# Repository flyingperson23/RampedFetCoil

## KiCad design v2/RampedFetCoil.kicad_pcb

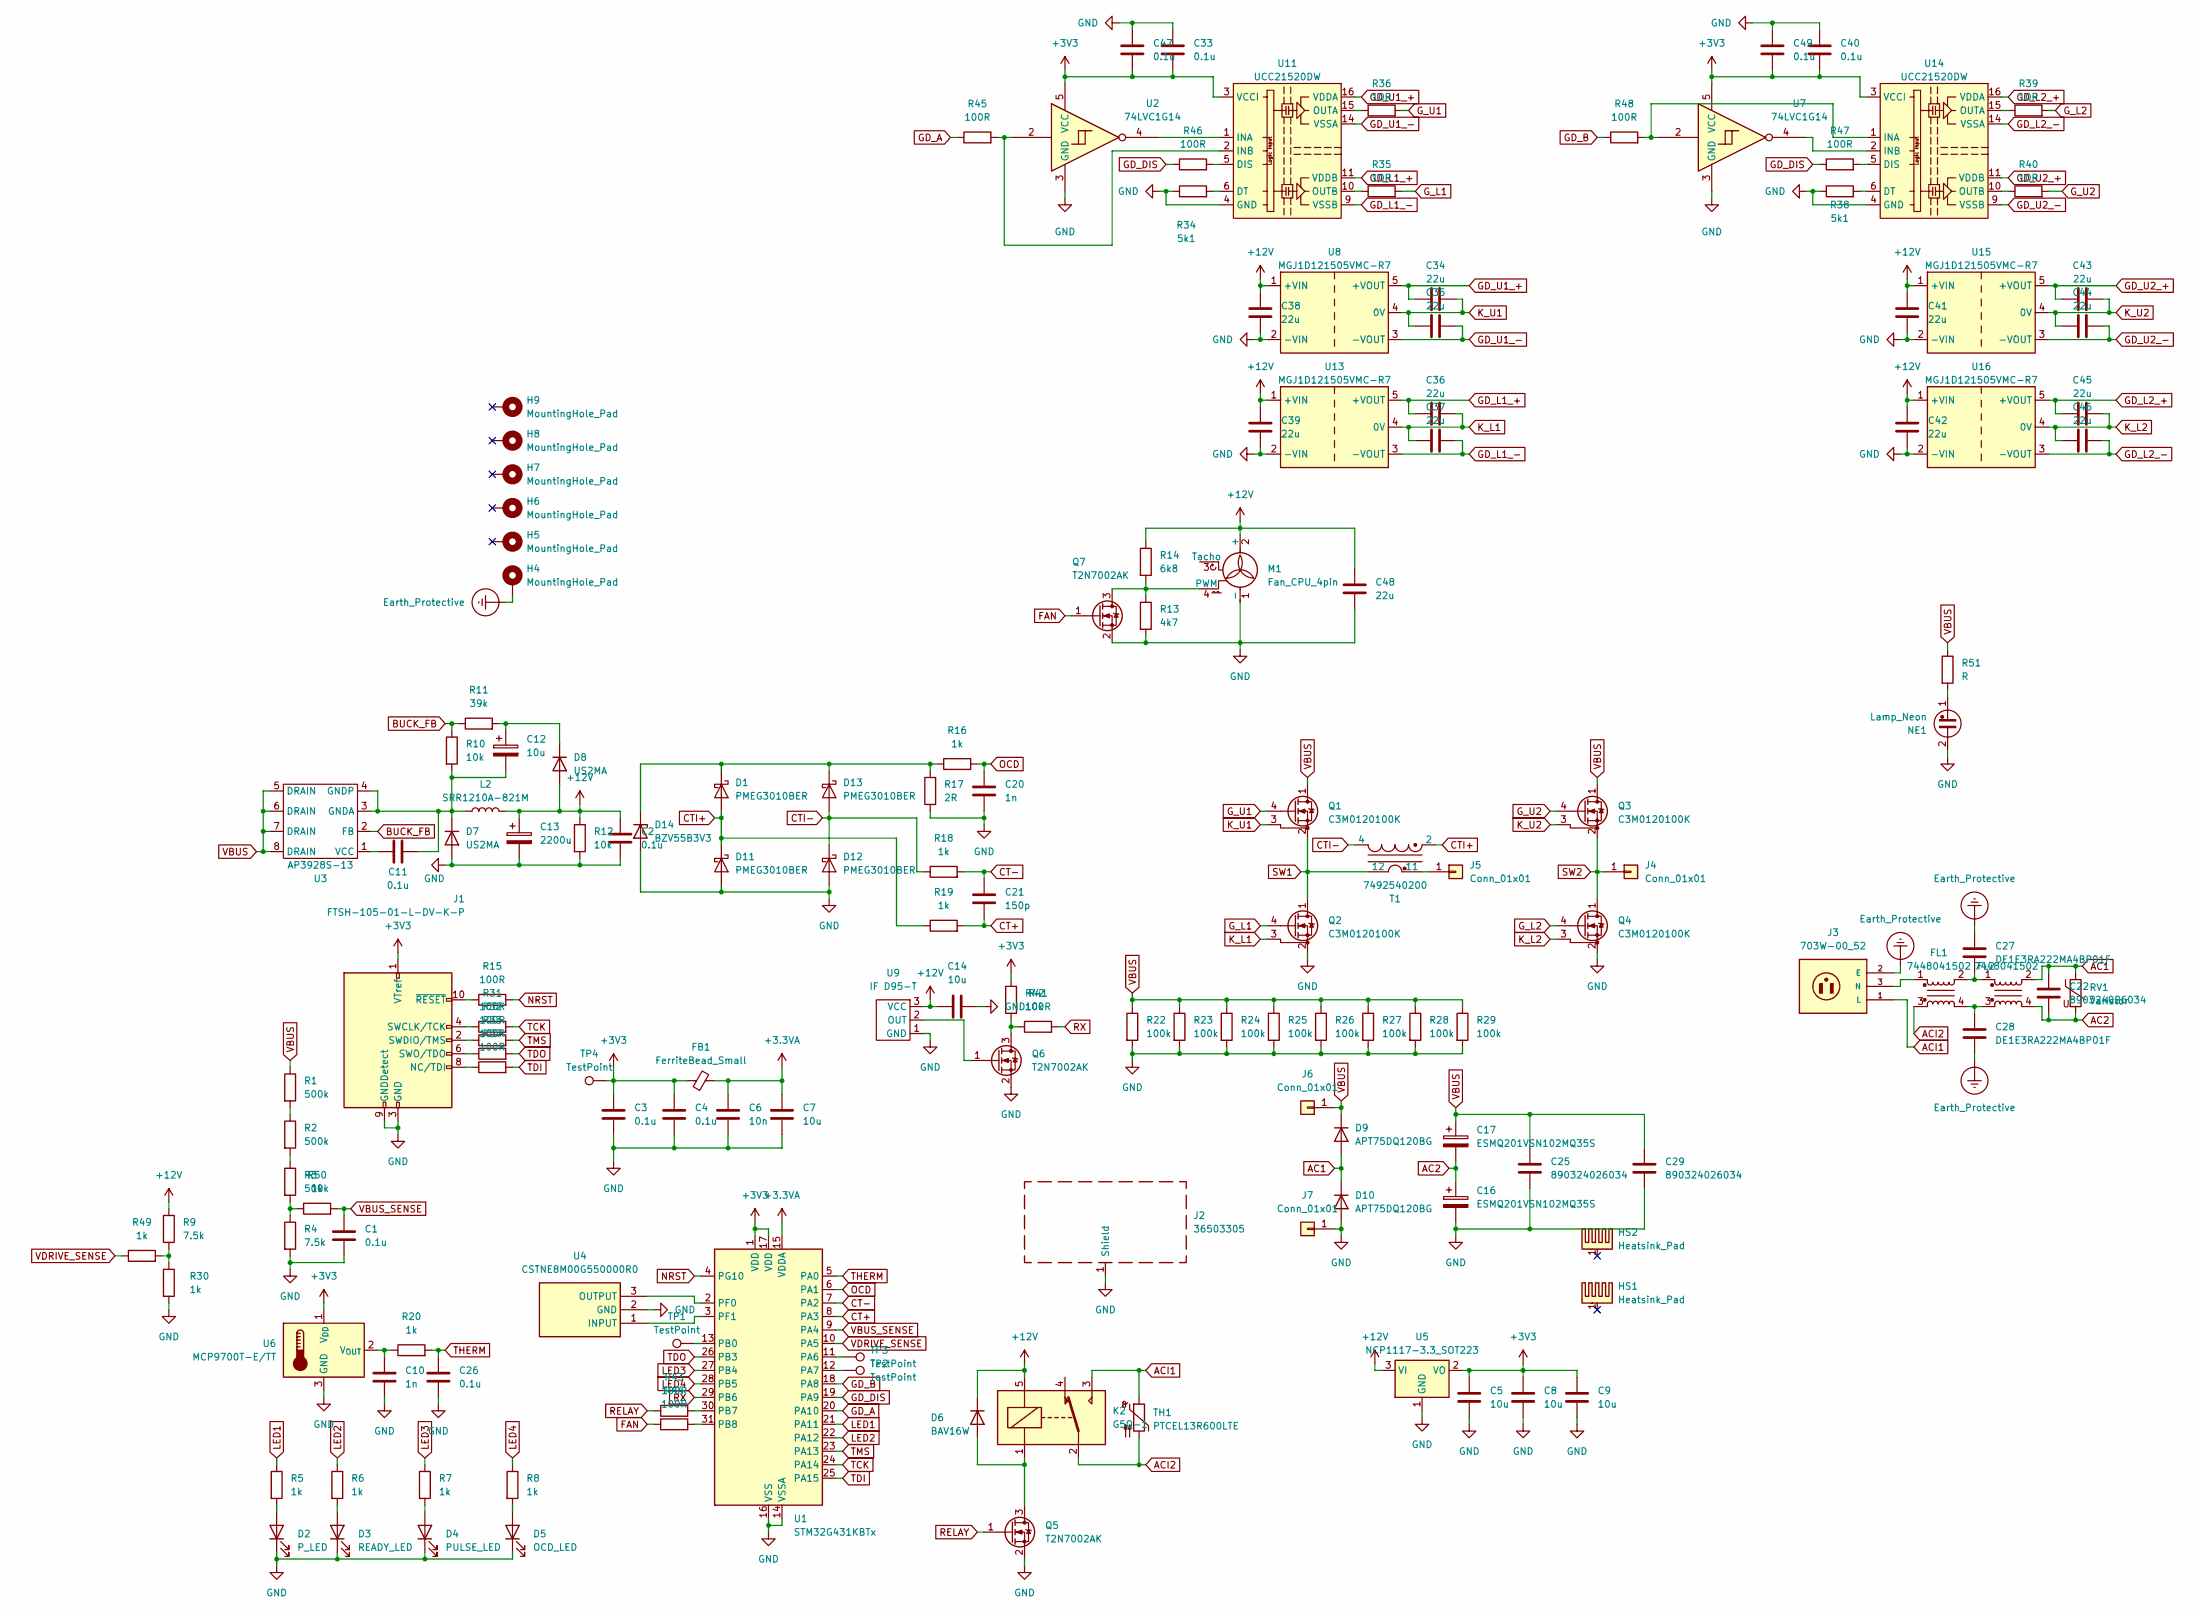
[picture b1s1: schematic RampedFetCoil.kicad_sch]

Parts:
C1, C2, C3, C4, C11, C26, C33, C40, C47, C49: 0.1u; C_0805_2012Metric
C5, C7, C8, C9, C14: 10u; C_0805_2012Metric
C6: 10n; C_0805_2012Metric
C10, C20: 1n; C_0805_2012Metric
C12: 10u; 860010572002; MPN 860010572002
C13: 2200u; 2m2 25V 860010478021; MPN 860020575013
C16, C17: ESMQ201VSN102MQ35S
C21: 150p; C_0805_2012Metric
C22, C25, C29: 890324026034
C27, C28: DE1E3RA222MA4BP01F
C34, C35, C36, C37, C38, C39, C41, C42, C43, C44, C45, C46, C48: 22u; C_1210_3225Metric
D1, D11, D12, D13: PMEG3010BER; Nexperia_CFP3_SOD-123W
D2: P_LED; LED_0805_2012Metric
D3: READY_LED; LED_0805_2012Metric
D4: PULSE_LED; LED_0805_2012Metric
D5: OCD_LED; LED_0805_2012Metric
D6: BAV16W; D_SOD-123
D7, D8: US2MA; D_SMA
D9, D10: APT75DQ120BG; TO-247-2_Vertical
D14: BZV55B3V3; D_MiniMELF
FB1: FerriteBead_Small; L_0805_2012Metric
FL1, FL2: 7448041502
H4, H5, H6, H7, H8, H9: MountingHole_Pad; MountingHole_4.3mm_M4_Pad_Via
HS1: Heatsink_Pad; C40
HS2: Heatsink_Pad; C40_Half
J1: FTSH-105-01-L-DV-K-P; PinHeader_2x05_P1.27mm_Vertical_SMD
J2: 36503305; Wuerth_36503305_30x30mm
J3: 703W-00_52; QUALTEK_703W-00_52; PARTREV B
J4, J5, J6, J7: Conn_01x01; SPADE_726386-2
K2: G5Q-1; Relay_SPDT_Omron-G5Q-1
L2: SRR1210A-821M; L_Bourns_SRR1210A
M1: Fan_CPU_4pin; FanPinHeader_1x04_P2.54mm_Vertical
NE1: Lamp_Neon; NEON-A1A
Q1, Q2, Q3, Q4: C3M0120100K; TO-247-4_Vertical
Q5, Q6, Q7: T2N7002AK; SOT-23
R1, R2, R3: 500k; R_0805_2012Metric
R4, R9: 7.5k; R_0805_2012Metric
R5, R6, R7, R8, R16, R18, R19, R20, R30, R49, R50: 1k; R_0805_2012Metric
R10, R12, R42: 10k; R_0805_2012Metric
R11: 39k; R_0805_2012Metric
R13: 4k7; R_0805_2012Metric
R14: 6k8; R_0805_2012Metric
R15, R31, R32, R33, R37, R41, R43, R44, R45, R46, R47, R48: 100R; R_0805_2012Metric
R17: 2R; R_2512_6332Metric
R22, R23, R24, R25, R26, R27, R28, R29: 100k; R_2512_6332Metric
R34, R38: 5k1; R_0805_2012Metric
R35, R36, R39, R40: 10R; R_0805_2012Metric
R51: R; R_Axial_DIN0207_L6.3mm_D2.5mm_P2.54mm_Vertical
RV1: Varistor; RV_Disc_D15.5mm_W3.9mm_P7.5mm
T1: 7492540200
TH1: PTCEL13R600LTE; THERMISTOR_PTCEL13_5MM_VIS
TP1, TP2, TP3, TP4: TestPoint; TestPoint_Pad_1.5x1.5mm
U1: STM32G431KBTx; LQFP-32_7x7mm_P0.8mm
U2, U7: 74LVC1G14; SOT-23-5
U3: AP3928S-13; SO-8_3.9x4.9mm_P1.27mm
U4: CSTNE8M00G550000R0; Resonator_SMD_Murata_CSTxExxV-3Pin_3.0x1.1mm; Mouser Part Number 81-CSTNE8M00G550000R
U5: NCP1117-3.3_SOT223; SOT-223-3_TabPin2
U6: MCP9700T-E/TT; SOT-23
U8, U13, U15, U16: MGJ1D121505VMC-R7; MGJ1V
U9: IF D95-T; IF-D95
U11, U14: UCC21520DW; SOIC-16W_7.5x10.3mm_P1.27mm

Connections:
+3.3VA: C6.1, C7.1, FB1.2, U1.15 (VDDA)
+3V3: C3.1, C4.1, C5.1, C8.1, C9.1, C33.2, C40.2, C47.2, C49.2, FB1.1, J1.1 (VTref), R42.2, TP4.1, U1.1 (VDD), U1.17 (VDD), U2.5 (VCC), U5.2 (VO), U6.1 (V_{DD}), U7.5 (VCC), U11.3 (VCCI), U11.8 (VCCI), U14.3 (VCCI), U14.8 (VCCI)
+12V: C2.1, C13.1, C14.1, C38.2, C39.2, C41.2, C42.2, C48.2, D6.1 (K), D8.2 (A), K2.5, L2.2, M1.2 (+), R9.1, R12.1, R14.1, U5.3 (VI), U8.1 (+VIN), U9.3 (VCC), U13.1 (+VIN), U15.1 (+VIN), U16.1 (+VIN)
AC1: C22.1, D9.2 (A), D10.1 (K), FL2.2, RV1.1
AC2: C16.1, C17.2, C22.2, FL2.4, RV1.2
ACI1: J3.1 (L), K2.3, TH1.1
ACI2: FL1.3, K2.2, TH1.2
BUCK_FB: R10.1, R11.1, U3.2 (FB)
CT+: C21.2, R19.2, U1.8 (PA3)
CT-: C21.1, R18.2, U1.7 (PA2)
CTI+: D1.2 (A), D11.1 (K), R19.1, T1.2
CTI-: D12.1 (K), D13.2 (A), R18.1, T1.4
Earth_Protective: C27.1, C28.2, H4.1, J3.2 (E)
FAN: Q7.1 (G), R44.1
GD_A: R45.1, U1.20 (PA10)
GD_B: R48.1, U1.18 (PA8)
GD_DIS: R46.1, R47.1, U1.19 (PA9)
GD_L1_+: C36.1, U11.11 (VDDB), U13.5 (+VOUT)
GD_L1_-: C37.2, U11.9 (VSSB), U13.3 (-VOUT)
GD_L2_+: C45.1, U14.16 (VDDA), U16.5 (+VOUT)
GD_L2_-: C46.2, U14.14 (VSSA), U16.3 (-VOUT)
GD_U1_+: C34.1, U8.5 (+VOUT), U11.16 (VDDA)
GD_U1_-: C35.2, U8.3 (-VOUT), U11.14 (VSSA)
GD_U2_+: C43.1, U14.11 (VDDB), U15.5 (+VOUT)
GD_U2_-: C44.2, U14.9 (VSSB), U15.3 (-VOUT)
GND: C1.2, C2.2, C3.2, C4.2, C5.2, C6.2, C7.2, C8.2, C9.2, C10.2, C13.2, C14.2, C16.2, C20.2, C25.2, C26.2, C29.2, C33.1, C38.1, C39.1, C40.1, C41.1, C42.1, C47.1, C48.1, C49.1, D2.1 (K), D3.1 (K), D4.1 (K), D5.1 (K), D7.2 (A), D10.2 (A), D11.2 (A), D12.2 (A), D14.2 (A), J1.3 (GND), J1.5 (GND), J1.9 (GNDDetect), J2.1 (Shield), J7.1, M1.1 (-), NE1.2, Q2.2 (S), Q4.2 (S), Q5.2 (S), Q6.2 (S), Q7.2 (S), R4.2, R12.2, R13.2, R17.1, R22.2, R23.2, R24.2, R25.2, R26.2, R27.2, R28.2, R29.2, R30.2, R34.1, R38.1, U1.14 (VSSA), U1.16 (VSS), U1.32 (VSS), U2.3 (GND), U4.2 (GND), U5.1 (GND), U6.3 (GND), U7.3 (GND), U8.2 (-VIN), U9.1 (GND), U11.4 (GND), U13.2 (-VIN), U14.4 (GND), U15.2 (-VIN), U16.2 (-VIN)
G_L1: Q2.4 (G), R35.2
G_L2: Q4.4 (G), R39.2
G_U1: Q1.4 (G), R36.2
G_U2: Q3.4 (G), R40.2
K_L1: C36.2, C37.1, Q2.3 (DS), U13.4 (0V)
K_L2: C45.2, C46.1, Q4.3 (DS), U16.4 (0V)
K_U1: C34.2, C35.1, Q1.3 (DS), U8.4 (0V)
K_U2: C43.2, C44.1, Q3.3 (DS), U15.4 (0V)
LED1: R5.1, U1.21 (PA11)
LED2: R6.1, U1.22 (PA12)
LED3: R7.1, U1.27 (PB4)
LED4: R8.1, U1.28 (PB5)
NRST: R15.2, U1.4 (PG10)
unnamed: C27.2, FL1.2, FL2.1
unnamed: C28.1, FL1.4, FL2.3
unnamed: D1.1 (K), D13.1 (K), D14.1 (K), R16.1, R17.2
unnamed: D2.2 (A), R5.2
unnamed: D3.2 (A), R6.2
unnamed: D4.2 (A), R7.2
unnamed: D5.2 (A), R8.2
unnamed: D6.2 (A), K2.1, Q5.3 (D)
unnamed: C11.1, C12.2, D7.1 (K), L2.1, R10.2, U3.3 (GNDA), U3.4 (GNDP)
unnamed: C12.1, D8.1 (K), R11.2
unnamed: J1.8 (NC/TDI), R37.1
unnamed: J1.4 (SWCLK/TCK), R31.1
unnamed: J1.2 (SWDIO/TMS), R32.1
unnamed: J1.6 (SWO/TDO), R33.1
unnamed: J1.10 (~RESET), R15.1
unnamed: FL1.1, J3.3 (N)
unnamed: J5.1, T1.11
unnamed: M1.4 (PWM), Q7.3 (D), R13.1, R14.2
unnamed: NE1.1, R51.2
unnamed: Q6.3 (D), R41.1, R42.1
unnamed: Q6.1 (G), U9.2 (OUT)
unnamed: R1.2, R2.1
unnamed: R2.2, R3.1
unnamed: R3.2, R4.1, R50.1
unnamed: R9.2, R30.1, R49.2
unnamed: TP3.1, U1.11 (PA6)
unnamed: TP2.1, U1.12 (PA7)
unnamed: TP1.1, U1.13 (PB0)
unnamed: R43.2, U1.30 (PB7)
unnamed: R44.2, U1.31 (PB8)
unnamed: U1.2 (PF0), U4.3 (OUTPUT)
unnamed: U1.3 (PF1), U4.1 (INPUT)
unnamed: C11.2, U3.1 (VCC)
unnamed: C10.1, R20.1, U6.2 (V_{OUT})
unnamed: R46.2, U11.5 (DIS)
unnamed: R34.2, U11.6 (DT)
unnamed: U2.4, U11.1 (INA)
unnamed: R45.2, U2.2, U11.2 (INB)
unnamed: R36.1, U11.15 (OUTA)
unnamed: R35.1, U11.10 (OUTB)
unnamed: R47.2, U14.5 (DIS)
unnamed: R38.2, U14.6 (DT)
unnamed: R48.2, U7.2, U14.1 (INA)
unnamed: U7.4, U14.2 (INB)
unnamed: R39.1, U14.15 (OUTA)
unnamed: R40.1, U14.10 (OUTB)
OCD: C20.1, R16.2, U1.6 (PA1)
RELAY: Q5.1 (G), R43.1
RX: R41.2, U1.29 (PB6)
SW1: Q1.2 (S), Q2.1 (D), T1.12
SW2: J4.1, Q3.2 (S), Q4.1 (D)
TCK: R31.2, U1.24 (PA14)
TDI: R37.2, U1.25 (PA15)
TDO: R33.2, U1.26 (PB3)
THERM: C26.1, R20.2, U1.5 (PA0)
TMS: R32.2, U1.23 (PA13)
VBUS: C17.1, C25.1, C29.1, D9.1 (K), J6.1, Q1.1 (D), Q3.1 (D), R1.1, R22.1, R23.1, R24.1, R25.1, R26.1, R27.1, R28.1, R29.1, R51.1, U3.5 (DRAIN), U3.6 (DRAIN), U3.7 (DRAIN), U3.8 (DRAIN)
VBUS_SENSE: C1.1, R50.2, U1.9 (PA4)
VDRIVE_SENSE: R49.1, U1.10 (PA5)

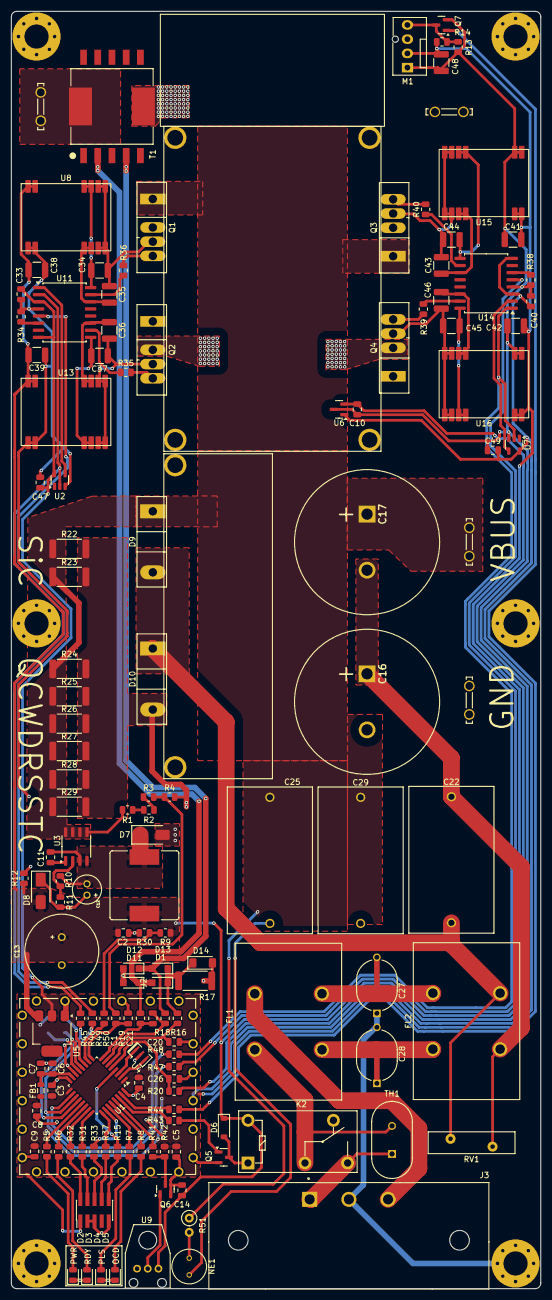
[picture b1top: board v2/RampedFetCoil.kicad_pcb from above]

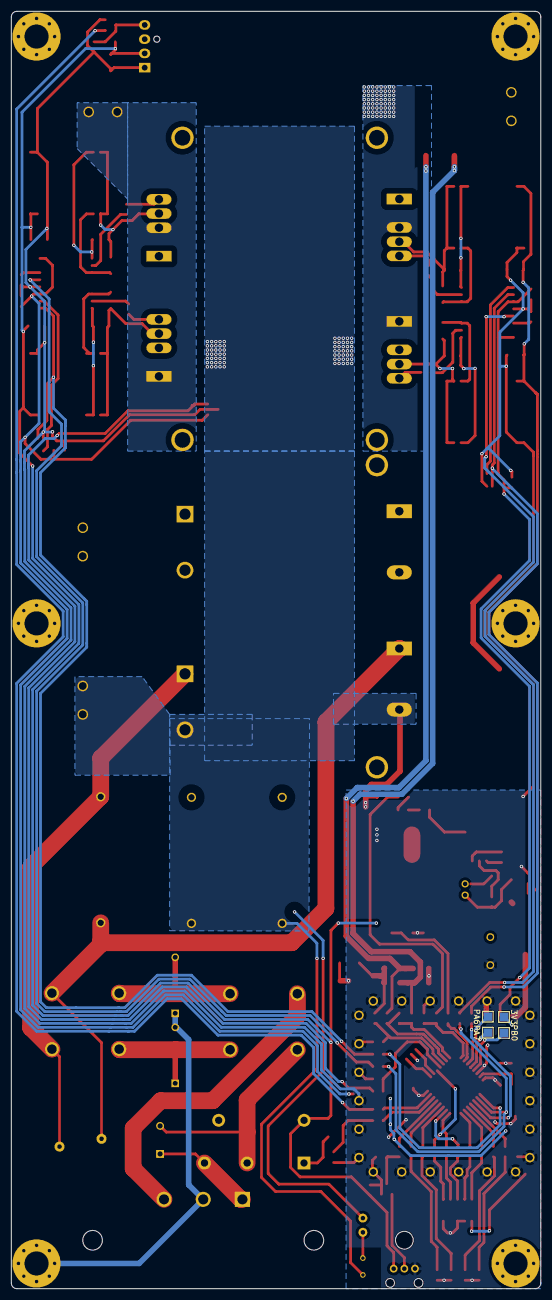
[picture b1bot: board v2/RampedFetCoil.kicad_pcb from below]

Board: 2 copper layers, 94.5 x 228.0 mm, 155 parts (4 on the bottom side), 98 nets.

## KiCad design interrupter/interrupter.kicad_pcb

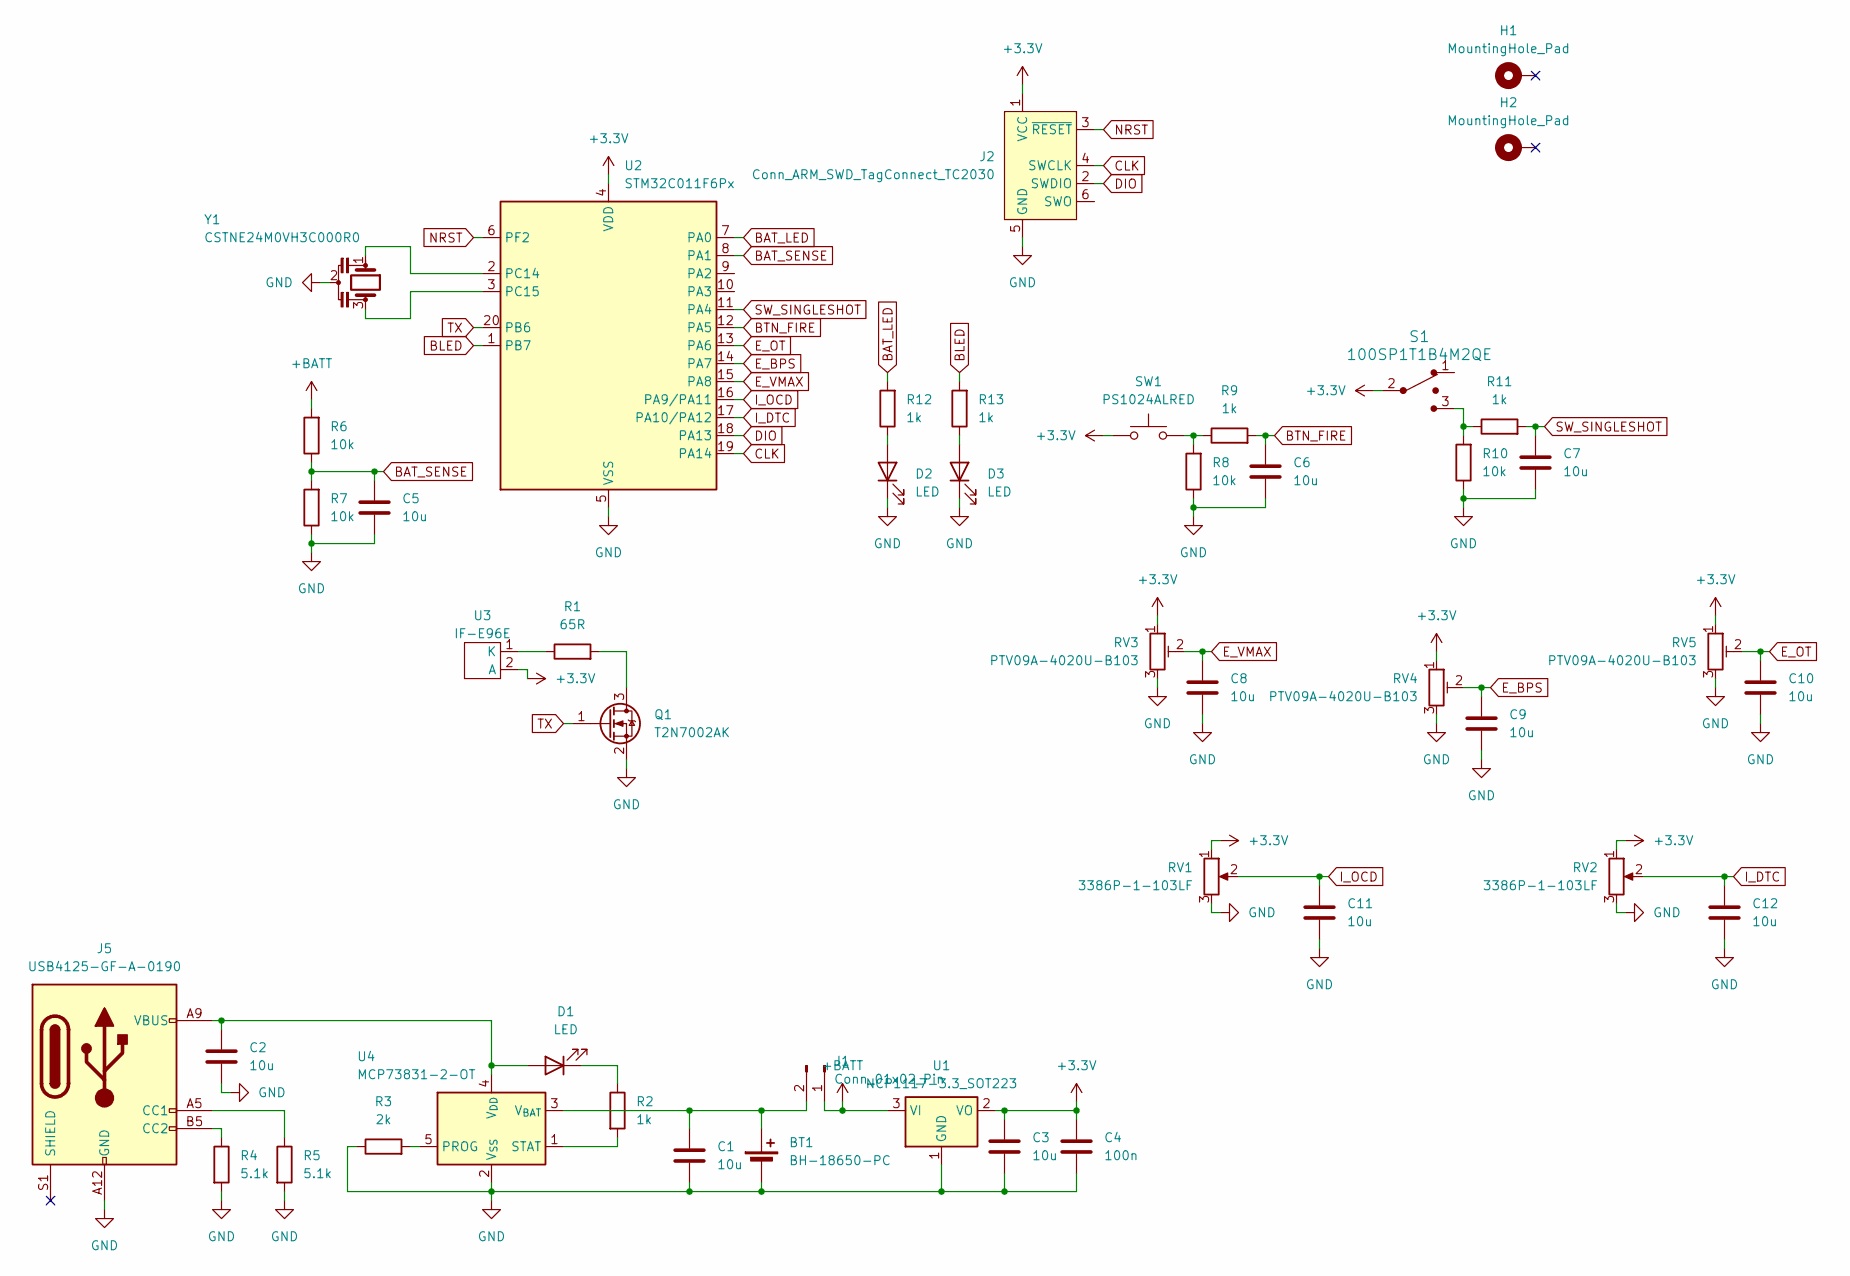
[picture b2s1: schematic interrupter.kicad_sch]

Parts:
BT1: BH-18650-PC; BatteryHolder_MPD_BH-18650-PC2
C1, C2, C3, C5, C6, C7, C8, C9, C10, C11, C12: 10u; C_0805_2012Metric
C4: 100n; C_0805_2012Metric
D1, D2, D3: LED; LED_0805_2012Metric
H1, H2: MountingHole_Pad; MountingHole_2.7mm_M2.5_Pad_Via
J1: Conn_01x02_Pin; Molex_KK-254_AE-6410-02A_1x02_P2.54mm_Vertical
J2: Conn_ARM_SWD_TagConnect_TC2030; Tag-Connect_TC2030-IDC-FP_2x03_P1.27mm_Vertical
J5: USB4125-GF-A-0190; USB_C_Receptacle_GCT_USB4125-xx-x-0190_6P_TopMnt_Horizontal
Q1: T2N7002AK; SOT-23
R1: 65R; R_0805_2012Metric
R2, R9, R11, R12, R13: 1k; R_0805_2012Metric
R3: 2k; R_0805_2012Metric
R4, R5: 5.1k; R_0805_2012Metric
R6, R7, R8, R10: 10k; R_0805_2012Metric
RV1, RV2: 3386P-1-103LF; Potentiometer_Bourns_3386P_Vertical
RV3, RV4, RV5: PTV09A-4020U-B103; Potentiometer_Bourns_PTV09A-1_Single_Vertical
S1: 100SP1T1B4M2QE; Toggle_Switch_100SP1T1B4M2QE; MPN 100SP1T1B4M2QE; Digi-Key_PN EG2355-ND
SW1: PS1024ALRED; SW_PS1024ALRED
U1: NCP1117-3.3_SOT223; SOT-223-3_TabPin2
U2: STM32C011F6Px; TSSOP-20_4.4x6.5mm_P0.65mm
U3: IF-E96E
U4: MCP73831-2-OT; SOT-23-5
Y1: CSTNE24M0VH3C000R0; Resonator_SMD_Murata_CSTxExxV-3Pin_3.0x1.1mm

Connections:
+3.3V: C3.1, C4.1, J2.1 (VCC), RV1.1, RV2.1, RV3.1, RV4.1, RV5.1, S1.2 (Com), SW1.1, U1.2 (VO), U2.4 (VDD), U3.2 (A)
+BATT: J1.1, R6.2, U1.3 (VI)
BAT_LED: R12.2, U2.7 (PA0)
BAT_SENSE: C5.1, R6.1, R7.2, U2.8 (PA1)
BLED: R13.2, U2.1 (PB7)
BTN_FIRE: C6.1, R9.2, U2.12 (PA5)
CLK: J2.4 (SWCLK), U2.19 (PA14)
DIO: J2.2 (SWDIO), U2.18 (PA13)
E_BPS: C9.1, RV4.2, U2.14 (PA7)
E_OT: C10.1, RV5.2, U2.13 (PA6)
E_VMAX: C8.1, RV3.2, U2.15 (PA8)
GND: BT1.2 (-), C1.2, C2.2, C3.2, C4.2, C5.2, C6.2, C7.2, C8.2, C9.2, C10.2, C11.2, C12.2, D2.1 (K), D3.1 (K), J2.5 (GND), J5.A12 (GND), J5.B12 (GND), Q1.2 (S), R3.1, R4.2, R5.2, R7.1, R8.1, R10.1, RV1.3, RV2.3, RV3.3, RV4.3, RV5.3, U1.1 (GND), U2.5 (VSS), U4.2 (V_{SS}), Y1.2
I_DTC: C12.1, RV2.2, U2.17 (PA10/PA12)
I_OCD: C11.1, RV1.2, U2.16 (PA9/PA11)
NRST: J2.3 (~RESET), U2.6 (PF2)
unnamed: BT1.1 (+), C1.1, J1.2, U4.3 (V_{BAT})
unnamed: C2.1, D1.2 (A), J5.A9 (VBUS), J5.B9 (VBUS), U4.4 (V_{DD})
unnamed: D1.1 (K), R2.1
unnamed: D2.2 (A), R12.1
unnamed: D3.2 (A), R13.1
unnamed: J5.A5 (CC1), R5.1
unnamed: J5.B5 (CC2), R4.1
unnamed: Q1.3 (D), R1.2
unnamed: R8.2, R9.1, SW1.2
unnamed: R10.2, R11.1, S1.3
unnamed: U2.2 (PC14), Y1.1
unnamed: U2.3 (PC15), Y1.3
unnamed: R1.1, U3.1 (K)
unnamed: R3.2, U4.5 (PROG)
unnamed: R2.2, U4.1 (STAT)
SW_SINGLESHOT: C7.1, R11.2, U2.11 (PA4)
TX: Q1.1 (G), U2.20 (PB6)

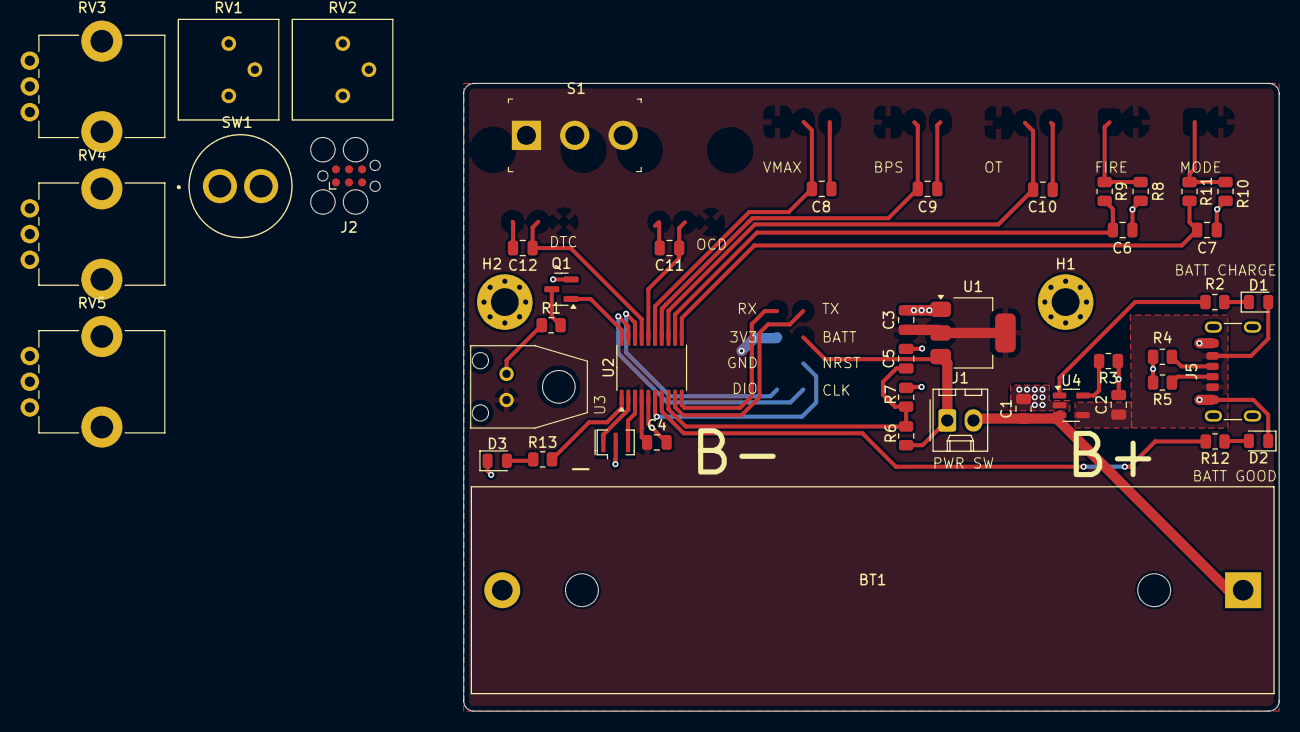
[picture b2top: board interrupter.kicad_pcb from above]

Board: 2 copper layers, 79.2 x 61.0 mm, 47 parts (0 on the bottom side), 32 nets.

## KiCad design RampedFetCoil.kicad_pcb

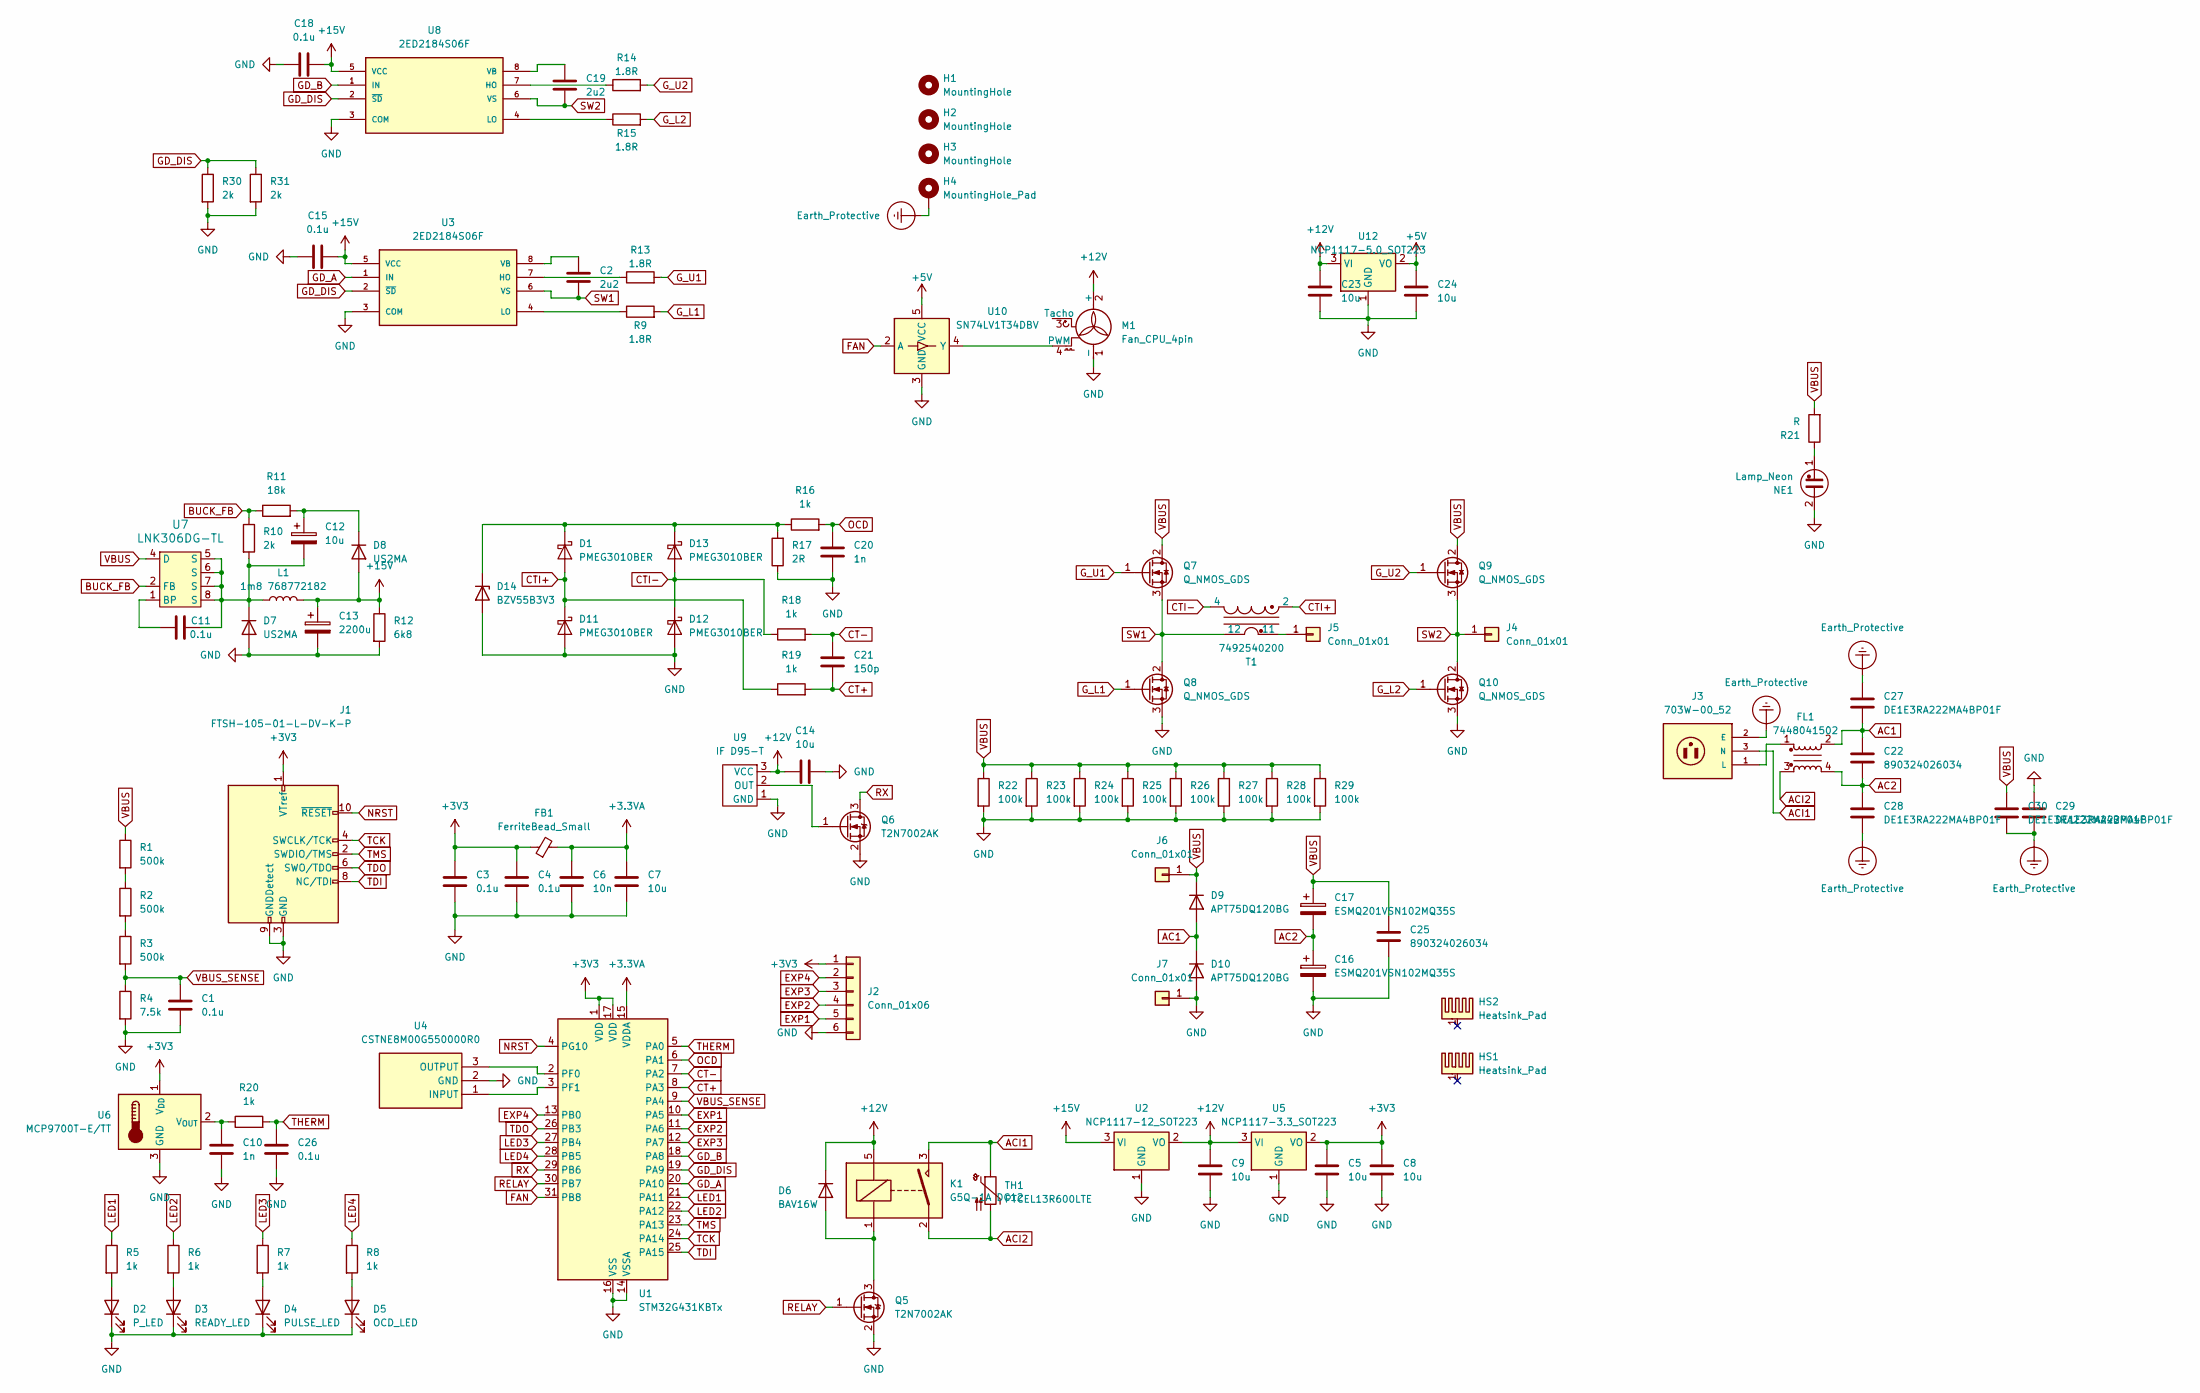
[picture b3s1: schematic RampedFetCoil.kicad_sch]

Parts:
C1, C3, C4, C11, C15, C18, C26: 0.1u; C_0805_2012Metric
C2, C19: 2u2; C_0805_2012Metric
C5, C7, C8, C9, C14, C23, C24: 10u; C_0805_2012Metric
C6: 10n; C_0805_2012Metric
C10, C20: 1n; C_0805_2012Metric
C12: 10u; 860010572002; MPN 860010572002
C13: 2200u; 2m2 25V 860010478021; MPN 860020575013
C16, C17: ESMQ201VSN102MQ35S
C21: 150p; C_0805_2012Metric
C22, C25: 890324026034
C27, C28, C29, C30: DE1E3RA222MA4BP01F
D1, D11, D12, D13: PMEG3010BER; Nexperia_CFP3_SOD-123W
D2: P_LED; LED_0805_2012Metric
D3: READY_LED; LED_0805_2012Metric
D4: PULSE_LED; LED_0805_2012Metric
D5: OCD_LED; LED_0805_2012Metric
D6: BAV16W; D_SOD-123
D7, D8: US2MA; D_SMA
D9, D10: APT75DQ120BG; TO-247-2_Vertical
D14: BZV55B3V3; D_MiniMELF
FB1: FerriteBead_Small; L_0805_2012Metric
FL1: 7448041502
H1, H2, H3: MountingHole; MountingHole_4.3mm_M4
H4: MountingHole_Pad; MountingHole_4.3mm_M4_Pad_Via
HS1: Heatsink_Pad; C40
HS2: Heatsink_Pad; C40_Half
J1: FTSH-105-01-L-DV-K-P; PinHeader_2x05_P1.27mm_Vertical_SMD
J2: Conn_01x06; PinHeader_1x06_P2.54mm_Vertical
J3: 703W-00_52; QUALTEK_703W-00_52; PARTREV B
J4, J5, J6, J7: Conn_01x01; SPADE_726386-2
K1: G5Q-1A DC12; Relay_SPST_Omron-G5Q-1A
L1: 1m8 768772182; WE-TI_809591; MPN 768772182
M1: Fan_CPU_4pin; FanPinHeader_1x04_P2.54mm_Vertical
NE1: Lamp_Neon; NEON-A1A
Q5, Q6: T2N7002AK; SOT-23
Q7, Q8, Q9, Q10: Q_NMOS_GDS; TO-247-3_Vertical
R1, R2, R3: 500k; R_0805_2012Metric
R4: 7.5k; R_0805_2012Metric
R5, R6, R7, R8, R16, R18, R19, R20: 1k; R_0805_2012Metric
R9, R13, R14, R15: 1.8R; R_0805_2012Metric
R10, R30, R31: 2k; R_0805_2012Metric
R11: 18k; R_0805_2012Metric
R12: 6k8; R_0805_2012Metric
R17: 2R; R_2512_6332Metric
R21: R; R_Axial_DIN0207_L6.3mm_D2.5mm_P10.16mm_Horizontal
R22, R23, R24, R25, R26, R27, R28, R29: 100k; R_2512_6332Metric
T1: 7492540200
TH1: PTCEL13R600LTE; THERMISTOR_PTCEL13_5MM_VIS
U1: STM32G431KBTx; LQFP-32_7x7mm_P0.8mm
U2: NCP1117-12_SOT223; SOT-223-3_TabPin2
U3, U8: 2ED2184S06F; SOIC-8_3.9x4.9mm_P1.27mm; PARTREV 2.2
U4: CSTNE8M00G550000R0; Resonator_SMD_Murata_CSTxExxV-3Pin_3.0x1.1mm; Mouser Part Number 81-CSTNE8M00G550000R
U5: NCP1117-3.3_SOT223; SOT-223-3_TabPin2
U6: MCP9700T-E/TT; SOT-23
U7: LNK306DG-TL; PowerIntegrations_SO-8C; MPN LNK306DG-TL; Digi-Key_PN 596-1239-1-ND
U9: IF D95-T; IF-D95
U10: SN74LV1T34DBV; SOT-23-5
U12: NCP1117-5.0_SOT223; SOT-223-3_TabPin2

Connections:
+3.3VA: C6.1, C7.1, FB1.2, U1.15 (VDDA)
+3V3: C3.1, C4.1, C5.1, C8.1, FB1.1, J1.1 (VTref), J2.1, U1.1 (VDD), U1.17 (VDD), U5.2 (VO), U6.1 (V_{DD})
+5V: C24.1, U10.5 (VCC), U12.2 (VO)
+12V: C9.1, C14.1, C23.1, D6.1 (K), K1.5, M1.2 (+), U2.2 (VO), U5.3 (VI), U9.3 (VCC), U12.3 (VI)
+15V: C13.1, C15.2, C18.2, D8.2 (A), L1.2, R12.1, U2.3 (VI), U3.5 (VCC), U8.5 (VCC)
AC1: C22.1, C27.2, D9.2 (A), D10.1 (K), FL1.2
AC2: C16.1, C17.2, C22.2, C28.1, FL1.4
ACI1: J3.3 (N), K1.3, TH1.1
ACI2: FL1.3, K1.2, TH1.2
BUCK_FB: R10.1, R11.1, U7.2 (FB)
CT+: C21.2, R19.2, U1.8 (PA3)
CT-: C21.1, R18.2, U1.7 (PA2)
CTI+: D1.2 (A), D11.1 (K), R19.1, T1.2
CTI-: D12.1 (K), D13.2 (A), R18.1, T1.4
EXP1: J2.5, U1.10 (PA5)
EXP2: J2.4, U1.11 (PA6)
EXP3: J2.3, U1.12 (PA7)
EXP4: J2.2, U1.13 (PB0)
Earth_Protective: C27.1, C28.2, C29.2, C30.2, H4.1, J3.2 (E)
FAN: U1.31 (PB8), U10.2 (A)
GD_A: U1.20 (PA10), U3.1 (IN)
GD_B: U1.18 (PA8), U8.1 (IN)
GD_DIS: R30.1, R31.1, U1.19 (PA9), U3.2 (~SD), U8.2 (~SD)
GND: C1.2, C3.2, C4.2, C5.2, C6.2, C7.2, C8.2, C9.2, C10.2, C13.2, C14.2, C15.1, C16.2, C18.1, C20.2, C23.2, C24.2, C25.2, C26.2, C29.1, D2.1 (K), D3.1 (K), D4.1 (K), D5.1 (K), D7.2 (A), D10.2 (A), D11.2 (A), D12.2 (A), D14.2 (A), J1.3 (GND), J1.5 (GND), J1.9 (GNDDetect), J2.6, J7.1, M1.1 (-), NE1.2, Q5.2 (S), Q6.2 (S), Q8.3 (S), Q10.3 (S), R4.2, R12.2, R17.1, R22.2, R23.2, R24.2, R25.2, R26.2, R27.2, R28.2, R29.2, R30.2, R31.2, U1.14 (VSSA), U1.16 (VSS), U1.32 (VSS), U2.1 (GND), U3.3 (COM), U4.2 (GND), U5.1 (GND), U6.3 (GND), U8.3 (COM), U9.1 (GND), U10.3 (GND), U12.1 (GND)
G_L1: Q8.1 (G), R9.2
G_L2: Q10.1 (G), R15.2
G_U1: Q7.1 (G), R13.2
G_U2: Q9.1 (G), R14.2
LED1: R5.1, U1.21 (PA11)
LED2: R6.1, U1.22 (PA12)
LED3: R7.1, U1.27 (PB4)
LED4: R8.1, U1.28 (PB5)
NRST: J1.10 (~RESET), U1.4 (PG10)
unnamed: D1.1 (K), D13.1 (K), D14.1 (K), R16.1, R17.2
unnamed: D2.2 (A), R5.2
unnamed: D3.2 (A), R6.2
unnamed: D4.2 (A), R7.2
unnamed: D5.2 (A), R8.2
unnamed: D6.2 (A), K1.1, Q5.3 (D)
unnamed: C11.2, C12.2, D7.1 (K), L1.1, R10.2, U7.5 (S), U7.6 (S), U7.7 (S), U7.8 (S)
unnamed: C12.1, D8.1 (K), R11.2
unnamed: FL1.1, J3.1 (L)
unnamed: J5.1, T1.11
unnamed: M1.4 (PWM), U10.4 (Y)
unnamed: NE1.1, R21.1
unnamed: Q6.1 (G), U9.2 (OUT)
unnamed: R1.2, R2.1
unnamed: R2.2, R3.1
unnamed: U1.2 (PF0), U4.3 (OUTPUT)
unnamed: U1.3 (PF1), U4.1 (INPUT)
unnamed: R13.1, U3.7 (HO)
unnamed: R9.1, U3.4 (LO)
unnamed: C2.1, U3.8 (VB)
unnamed: C10.1, R20.1, U6.2 (V_{OUT})
unnamed: C11.1, U7.1 (BP)
unnamed: R14.1, U8.7 (HO)
unnamed: R15.1, U8.4 (LO)
unnamed: C19.1, U8.8 (VB)
OCD: C20.1, R16.2, U1.6 (PA1)
RELAY: Q5.1 (G), U1.30 (PB7)
RX: Q6.3 (D), U1.29 (PB6)
SW1: C2.2, Q7.3 (S), Q8.2 (D), T1.12, U3.6 (VS)
SW2: C19.2, J4.1, Q9.3 (S), Q10.2 (D), U8.6 (VS)
TCK: J1.4 (SWCLK/TCK), U1.24 (PA14)
TDI: J1.8 (NC/TDI), U1.25 (PA15)
TDO: J1.6 (SWO/TDO), U1.26 (PB3)
THERM: C26.1, R20.2, U1.5 (PA0)
TMS: J1.2 (SWDIO/TMS), U1.23 (PA13)
VBUS: C17.1, C25.1, C30.1, D9.1 (K), J6.1, Q7.2 (D), Q9.2 (D), R1.1, R21.2, R22.1, R23.1, R24.1, R25.1, R26.1, R27.1, R28.1, R29.1, U7.4 (D)
VBUS_SENSE: C1.1, R3.2, R4.1, U1.9 (PA4)

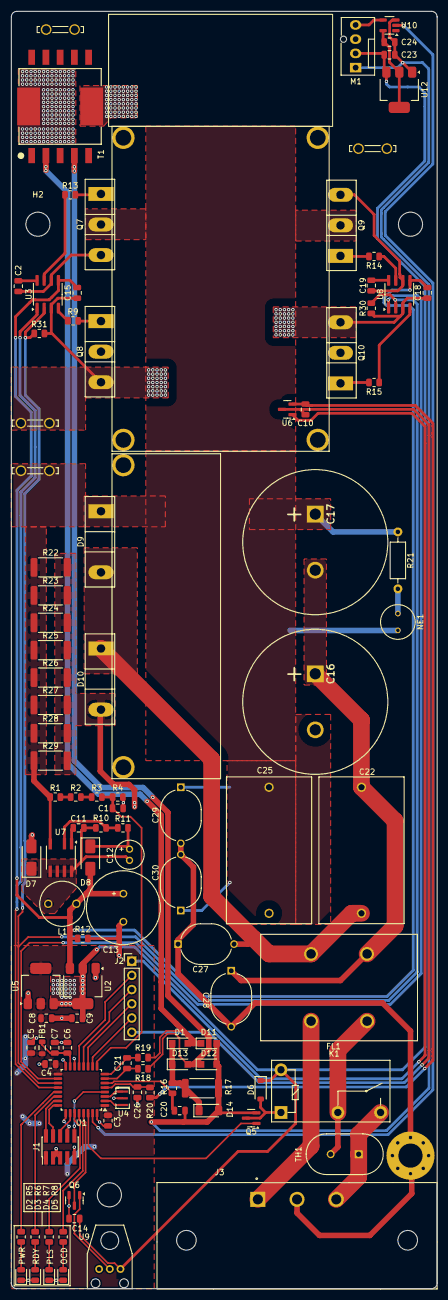
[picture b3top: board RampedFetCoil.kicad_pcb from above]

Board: 2 copper layers, 76.0 x 228.0 mm, 113 parts (0 on the bottom side), 70 nets.

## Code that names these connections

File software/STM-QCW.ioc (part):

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Mcu.Name=STM32G431K(6-8-B)Tx
Mcu.Package=LQFP32
Mcu.UserName=STM32G431KBTx
PA0.GPIOParameters=GPIO_Label
PA0.GPIO_Label=THERM
PA0.Mode=IN1-Single-Ended
PA0.Signal=ADC1_IN1
PA1.Mode=INP
PA1.Signal=COMP1_INP
PA10.GPIOParameters=GPIO_Label
PA10.GPIO_Label=GD_1
PA10.Signal=S_TIM1_CH3
PA11.GPIOParameters=GPIO_Label
PA11.GPIO_Label=LED1
PA11.Signal=S_TIM4_CH1
PA12.GPIOParameters=GPIO_Label
PA12.GPIO_Label=LED2
PA12.Signal=S_TIM4_CH2
PA13.Mode=JTAG_4_pins
PA13.Signal=SYS_JTMS-SWDIO
PA14.Mode=JTAG_4_pins
PA14.Signal=SYS_JTCK-SWCLK
PA15.Mode=JTAG_4_pins
PA15.Signal=SYS_JTDI
PA2.Mode=INM
PA2.Signal=COMP2_INM
PA3.Mode=INP
PA3.Signal=COMP2_INP
PA4.GPIOParameters=GPIO_Label
PA4.GPIO_Label=VBUS_SENSE
PA4.Mode=IN17-Single-Ended
PA4.Signal=ADC2_IN17
PA5.GPIOParameters=GPIO_Label
PA5.GPIO_Label=VDRIVE_SENSE
PA5.Mode=IN13-Single-Ended
PA5.Signal=ADC2_IN13
PA8.GPIOParameters=GPIO_Label
PA8.GPIO_Label=GD_2
PA8.Signal=S_TIM1_CH1
PA9.GPIOParameters=GPIO_Label
PA9.GPIO_Label=GD_DIS
PA9.Signal=GPIO_Output
PB3.Mode=JTAG_4_pins
PB3.Signal=SYS_JTDO-SWO
PB4.GPIOParameters=GPIO_Label
PB4.GPIO_Label=LED3
PB4.Signal=S_TIM3_CH1
PB5.GPIOParameters=GPIO_Label
PB5.GPIO_Label=LED4
PB5.Signal=S_TIM3_CH2
PB6.GPIOParameters=GPIO_PuPd,GPIO_Label
PB6.GPIO_Label=RX
PB6.GPIO_PuPd=GPIO_PULLUP
PB6.Mode=Half_duplex(single_wire_mode)
PB6.Signal=USART1_TX
PB7.GPIOParameters=GPIO_Label
PB7.GPIO_Label=RELAY
PB7.Signal=GPIO_Output
PB8-BOOT0.GPIOParameters=GPIO_PuPd,GPIO_Label
PB8-BOOT0.GPIO_Label=FAN
PB8-BOOT0.GPIO_PuPd=GPIO_PULLDOWN
PB8-BOOT0.Signal=S_TIM4_CH3
PF0-OSC_IN.Mode=HSE-External-Oscillator
PF0-OSC_IN.Signal=RCC_OSC_IN
PF1-OSC_OUT.Mode=HSE-External-Oscillator
PF1-OSC_OUT.Signal=RCC_OSC_OUT
RCC.HSE_Timout=1000
RCC.HSE_VALUE=8000000
RCC.SYSCLKFreq_VALUE=170000000
RCC.SYSCLKSource=RCC_SYSCLKSOURCE_PLLCLK
board=custom

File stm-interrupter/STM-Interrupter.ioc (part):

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Mcu.Name=STM32C011F(4-6)Px
Mcu.Package=TSSOP20
Mcu.UserName=STM32C011F6Px
PA0.GPIOParameters=GPIO_Label
PA0.GPIO_Label=BATT_LED
PA0.Signal=GPIO_Output
PA1.GPIOParameters=GPIO_Label
PA1.GPIO_Label=BATT_SENSE
PA1.Mode=IN1
PA1.Signal=ADC1_IN1
PA11\ [PA9].GPIOParameters=GPIO_Label
PA11\ [PA9].GPIO_Label=I_OCD
PA11\ [PA9].Mode=IN11
PA11\ [PA9].Signal=ADC1_IN11
PA12\ [PA10].GPIOParameters=GPIO_Label
PA12\ [PA10].GPIO_Label=I_DTC
PA12\ [PA10].Mode=IN12
PA12\ [PA10].Signal=ADC1_IN12
PA13.Mode=Serial_Wire
PA13.Signal=DEBUG_SWDIO
PA14-BOOT0.Mode=Serial_Wire
PA14-BOOT0.Signal=DEBUG_SWCLK
PA2.Mode=Asynchronous
PA2.Signal=USART2_TX
PA3.Mode=Asynchronous
PA3.Signal=USART2_RX
PA4.GPIOParameters=GPIO_Label
PA4.GPIO_Label=SW_SINGLESHOT
PA4.Signal=GPIO_Input
PA5.GPIOParameters=GPIO_Label
PA5.GPIO_Label=FIRE
PA5.Signal=GPIO_Input
PA6.GPIOParameters=GPIO_Label
PA6.GPIO_Label=E_OT
PA6.Mode=IN6
PA6.Signal=ADC1_IN6
PA7.GPIOParameters=GPIO_Label
PA7.GPIO_Label=E_BPS
PA7.Mode=IN7
PA7.Signal=ADC1_IN7
PA8.GPIOParameters=GPIO_Label
PA8.GPIO_Label=E_VMAX
PA8.Mode=IN8
PA8.Signal=ADC1_IN8
PB6.Mode=Half_duplex(single_wire_mode)
PB6.Signal=USART1_TX
PB7.GPIOParameters=GPIO_Label
PB7.GPIO_Label=BLED
PB7.Signal=GPIO_Output
PC14-OSCX_IN\ (PC14).Mode=HSE-External-Oscillator-REMAPPED
PC14-OSCX_IN\ (PC14).Signal=RCC_OSCX_IN
PC15-OSCX_OUT\ (PC15).Mode=HSE-External-Oscillator-REMAPPED
PC15-OSCX_OUT\ (PC15).Signal=RCC_OSCX_OUT
RCC.HSE_VALUE=24000000
RCC.SYSCLKFreq_VALUE=24000000
RCC.SYSCLKSource=RCC_SYSCLKSOURCE_HSE
board=custom

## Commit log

2025-04-06 init commit
2025-06-16 sicswap
2025-07-08 sicswap 2
2025-09-02 unsure
